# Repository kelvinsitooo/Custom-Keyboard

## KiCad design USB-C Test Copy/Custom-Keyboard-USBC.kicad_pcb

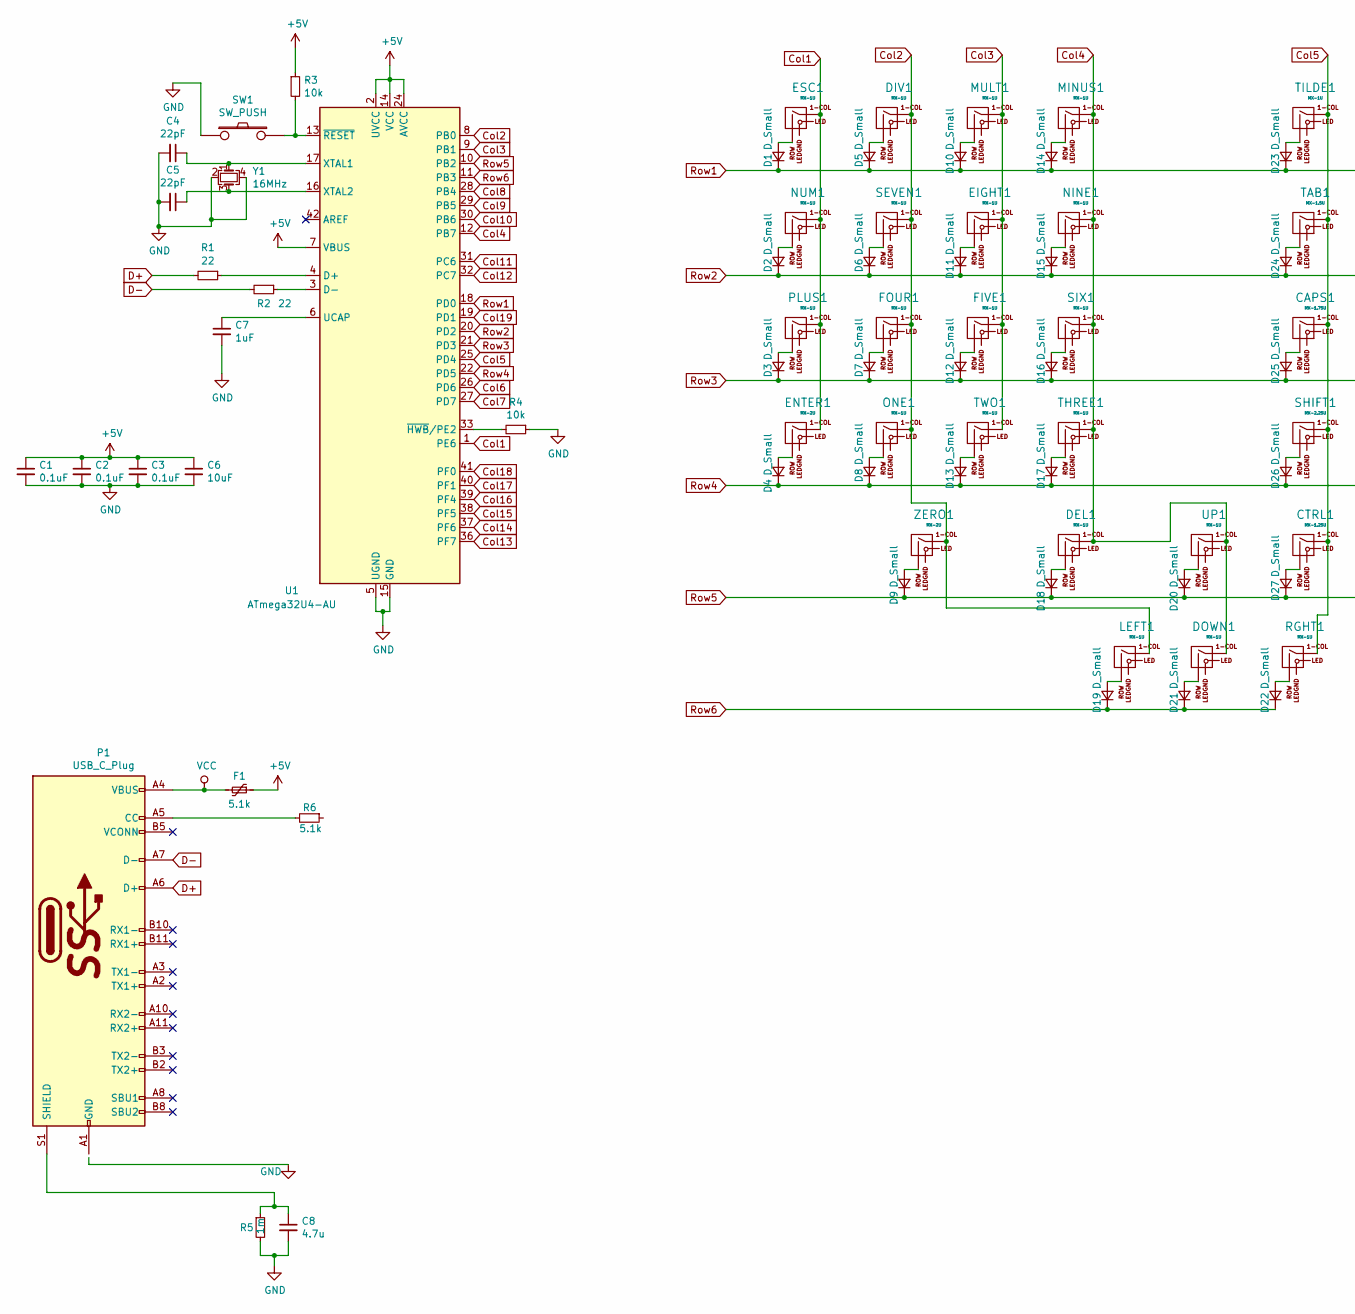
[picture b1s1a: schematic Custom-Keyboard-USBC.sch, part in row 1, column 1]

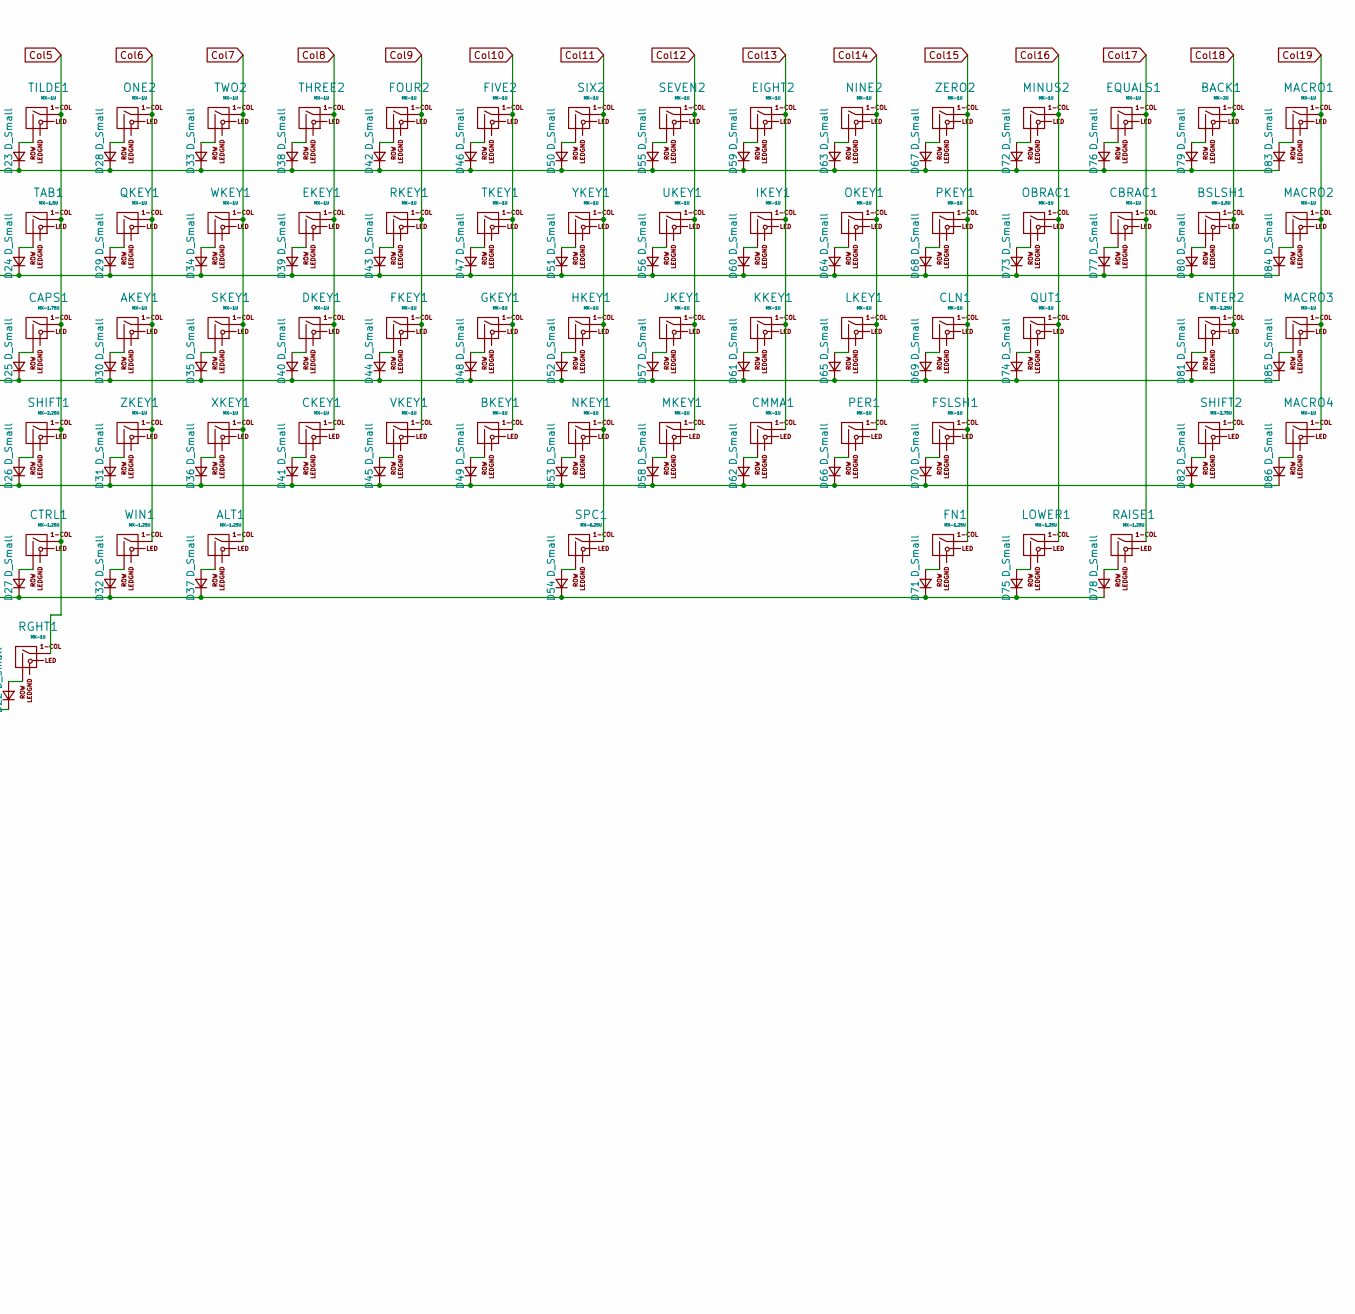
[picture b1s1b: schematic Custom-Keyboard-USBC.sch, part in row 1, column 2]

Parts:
AKEY1: MX-1U; MXOnly-1U-NoLED
ALT1: MX-1.25U; MXOnly-1.25U-NoLED
BACK1: MX-2U; MXOnly-2U-NoLED
BKEY1: MX-1U; MXOnly-1U-NoLED
BSLSH1: MX-1.5U; MXOnly-1.5U-NoLED
C1, C2, C3: 0.1uF; C_0805_2012Metric
C4, C5: 22pF; C_0805_2012Metric
C6: 10uF; C_0805_2012Metric
C7: 1uF; C_0805_2012Metric
C8: 4.7u; C_0805_2012Metric
CAPS1: MX-1.75U; MXOnly-1.75U-NoLED
CBRAC1: MX-1U; MXOnly-1U-NoLED
CKEY1: MX-1U; MXOnly-1U-NoLED
CLN1: MX-1U; MXOnly-1U-NoLED
CMMA1: MX-1U; MXOnly-1U-NoLED
CTRL1: MX-1.25U; MXOnly-1.25U-NoLED
D1, D2, D3, D4, D5, D6, D7, D8, D9, D10, D11, D12, D13, D14, D15, D16, D17, D18, D19, D20, D21, D22, D23, D24, D25, D26, D27, D28, D29, D30, D31, D32, D33, D34, D35, D36, D37, D38, D39, D40, D41, D42, D43, D44, D45, D46, D47, D48, D49, D50, D51, D52, D53, D54, D55, D56, D57, D58, D59, D60, D61, D62, D63, D64, D65, D66, D67, D68, D69, D70, D71, D72, D73, D74, D75, D76, D77, D78, D79, D80, D81, D82, D83, D84, D85, D86: D_Small; D_SOD-123
DEL1: MX-1U; MXOnly-1U-NoLED
DIV1: MX-1U; MXOnly-1U-NoLED
DKEY1: MX-1U; MXOnly-1U-NoLED
DOWN1: MX-1U; MXOnly-1U-NoLED
EIGHT1, EIGHT2: MX-1U; MXOnly-1U-NoLED
EKEY1: MX-1U; MXOnly-1U-NoLED
ENTER1: MX-2U; MXOnly-2U-NoLED
ENTER2: MX-2.25U; MXOnly-2.25U-NoLED
EQUALS1: MX-1U; MXOnly-1U-NoLED
ESC1: MX-1U; MXOnly-1U-NoLED
F1: 5.1k; Fuse_1206_3216Metric
FIVE1, FIVE2: MX-1U; MXOnly-1U-NoLED
FKEY1: MX-1U; MXOnly-1U-NoLED
FN1: MX-1.25U; MXOnly-1.25U-NoLED
FOUR1, FOUR2: MX-1U; MXOnly-1U-NoLED
FSLSH1: MX-1U; MXOnly-1U-NoLED
GKEY1: MX-1U; MXOnly-1U-NoLED
HKEY1: MX-1U; MXOnly-1U-NoLED
IKEY1: MX-1U; MXOnly-1U-NoLED
JKEY1: MX-1U; MXOnly-1U-NoLED
KKEY1: MX-1U; MXOnly-1U-NoLED
LEFT1: MX-1U; MXOnly-1U-NoLED
LKEY1: MX-1U; MXOnly-1U-NoLED
LOWER1: MX-1.25U; MXOnly-1.25U-NoLED
MACRO1, MACRO2, MACRO3, MACRO4: MX-1U; MXOnly-1U-NoLED
MINUS1, MINUS2: MX-1U; MXOnly-1U-NoLED
MKEY1: MX-1U; MXOnly-1U-NoLED
MULT1: MX-1U; MXOnly-1U-NoLED
NINE1, NINE2: MX-1U; MXOnly-1U-NoLED
NKEY1: MX-1U; MXOnly-1U-NoLED
NUM1: MX-1U; MXOnly-1U-NoLED
OBRAC1: MX-1U; MXOnly-1U-NoLED
OKEY1: MX-1U; MXOnly-1U-NoLED
ONE1, ONE2: MX-1U; MXOnly-1U-NoLED
P1: USB_C_Plug; USB-C-12-Pin-MidMount
PER1: MX-1U; MXOnly-1U-NoLED
PKEY1: MX-1U; MXOnly-1U-NoLED
PLUS1: MX-1U; MXOnly-1U-NoLED
QKEY1: MX-1U; MXOnly-1U-NoLED
QUT1: MX-1U; MXOnly-1U-NoLED
R1, R2: 22; R_0805_2012Metric
R3, R4: 10k; R_0805_2012Metric
R5: 1m; R_0805_2012Metric
R6: 5.1k; R_0805_2012Metric
RAISE1: MX-1.25U; MXOnly-1.25U-NoLED
RGHT1: MX-1U; MXOnly-1U-NoLED
RKEY1: MX-1U; MXOnly-1U-NoLED
SEVEN1, SEVEN2: MX-1U; MXOnly-1U-NoLED
SHIFT1: MX-2.25U; MXOnly-2.25U-NoLED
SHIFT2: MX-2.75U; MXOnly-2.75U-NoLED
SIX1, SIX2: MX-1U; MXOnly-1U-NoLED
SKEY1: MX-1U; MXOnly-1U-NoLED
SPC1: MX-6.25U; MXOnly-6.25U-NoLED
SW1: SW_PUSH; SKQG-1155865
TAB1: MX-1.5U; MXOnly-1.5U-NoLED
THREE1, THREE2: MX-1U; MXOnly-1U-NoLED
TILDE1: MX-1U; MXOnly-1U-NoLED
TKEY1: MX-1U; MXOnly-1U-NoLED
TWO1, TWO2: MX-1U; MXOnly-1U-NoLED
U1: ATmega32U4-AU; ATMEGA32U4-AU
UKEY1: MX-1U; MXOnly-1U-NoLED
UP1: MX-1U; MXOnly-1U-NoLED
VKEY1: MX-1U; MXOnly-1U-NoLED
WIN1: MX-1.25U; MXOnly-1.25U-NoLED
WKEY1: MX-1U; MXOnly-1U-NoLED
XKEY1: MX-1U; MXOnly-1U-NoLED
Y1: 16MHz; Crystal_SMD_3225-4Pin_3.2x2.5mm
YKEY1: MX-1U; MXOnly-1U-NoLED
ZERO1: MX-2U; MXOnly-2U-NoLED
ZERO2: MX-1U; MXOnly-1U-NoLED
ZKEY1: MX-1U; MXOnly-1U-NoLED

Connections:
+5V: C1.1, C2.1, C3.1, C6.1, F1.1, R3.1, U1.2 (UVCC), U1.7 (VBUS), U1.14 (VCC), U1.24 (AVCC), U1.34 (VCC), U1.44 (AVCC)
Col1: ENTER1.1 (COL), ESC1.1 (COL), NUM1.1 (COL), PLUS1.1 (COL), U1.1 (PE6)
Col2: DIV1.1 (COL), FOUR1.1 (COL), LEFT1.1 (COL), ONE1.1 (COL), SEVEN1.1 (COL), U1.8 (PB0), ZERO1.1 (COL)
Col3: EIGHT1.1 (COL), FIVE1.1 (COL), MULT1.1 (COL), TWO1.1 (COL), U1.9 (PB1)
Col4: DEL1.1 (COL), DOWN1.1 (COL), MINUS1.1 (COL), NINE1.1 (COL), SIX1.1 (COL), THREE1.1 (COL), U1.12 (PB7), UP1.1 (COL)
Col5: CAPS1.1 (COL), CTRL1.1 (COL), RGHT1.1 (COL), SHIFT1.1 (COL), TAB1.1 (COL), TILDE1.1 (COL), U1.25 (PD4)
Col6: AKEY1.1 (COL), ONE2.1 (COL), QKEY1.1 (COL), U1.26 (PD6), WIN1.1 (COL), ZKEY1.1 (COL)
Col7: ALT1.1 (COL), SKEY1.1 (COL), TWO2.1 (COL), U1.27 (PD7), WKEY1.1 (COL), XKEY1.1 (COL)
Col8: CKEY1.1 (COL), DKEY1.1 (COL), EKEY1.1 (COL), THREE2.1 (COL), U1.28 (PB4)
Col9: FKEY1.1 (COL), FOUR2.1 (COL), RKEY1.1 (COL), U1.29 (PB5), VKEY1.1 (COL)
Col10: BKEY1.1 (COL), FIVE2.1 (COL), GKEY1.1 (COL), TKEY1.1 (COL), U1.30 (PB6)
Col11: HKEY1.1 (COL), NKEY1.1 (COL), SIX2.1 (COL), SPC1.1 (COL), U1.31 (PC6), YKEY1.1 (COL)
Col12: JKEY1.1 (COL), MKEY1.1 (COL), SEVEN2.1 (COL), U1.32 (PC7), UKEY1.1 (COL)
Col13: CMMA1.1 (COL), EIGHT2.1 (COL), IKEY1.1 (COL), KKEY1.1 (COL), U1.36 (PF7)
Col14: LKEY1.1 (COL), NINE2.1 (COL), OKEY1.1 (COL), PER1.1 (COL), U1.37 (PF6)
Col15: CLN1.1 (COL), FN1.1 (COL), FSLSH1.1 (COL), PKEY1.1 (COL), U1.38 (PF5), ZERO2.1 (COL)
Col16: LOWER1.1 (COL), MINUS2.1 (COL), OBRAC1.1 (COL), QUT1.1 (COL), U1.39 (PF4)
Col17: CBRAC1.1 (COL), EQUALS1.1 (COL), RAISE1.1 (COL), U1.40 (PF1)
Col18: BACK1.1 (COL), BSLSH1.1 (COL), ENTER2.1 (COL), SHIFT2.1 (COL), U1.41 (PF0)
Col19: MACRO1.1 (COL), MACRO2.1 (COL), MACRO3.1 (COL), MACRO4.1 (COL), U1.19 (PD1)
D+: P1.A6 (D+), R1.2
D-: P1.A7 (D-), R2.2
GND: C1.2, C2.2, C3.2, C4.2, C5.2, C6.2, C7.2, C8.2, R4.1, R5.2, SW1.1, U1.5 (UGND), U1.15 (GND), U1.23 (GND), U1.35 (GND), U1.43 (GND), Y1.2, Y1.4
unnamed: AKEY1.2 (ROW), D30.2 (A)
unnamed: ALT1.2 (ROW), D37.2 (A)
unnamed: BACK1.2 (ROW), D79.2 (A)
unnamed: BKEY1.2 (ROW), D49.2 (A)
unnamed: BSLSH1.2 (ROW), D80.2 (A)
unnamed: C4.1, U1.17 (XTAL1), Y1.1
unnamed: C5.1, U1.16 (XTAL2), Y1.3
unnamed: C7.1, U1.6 (UCAP)
unnamed: C8.1, P1.S1 (SHIELD), R5.1
unnamed: CAPS1.2 (ROW), D25.2 (A)
unnamed: CBRAC1.2 (ROW), D77.2 (A)
unnamed: CKEY1.2 (ROW), D41.2 (A)
unnamed: CLN1.2 (ROW), D69.2 (A)
unnamed: CMMA1.2 (ROW), D62.2 (A)
unnamed: CTRL1.2 (ROW), D27.2 (A)
unnamed: D1.2 (A), ESC1.2 (ROW)
unnamed: D2.2 (A), NUM1.2 (ROW)
unnamed: D3.2 (A), PLUS1.2 (ROW)
unnamed: D4.2 (A), ENTER1.2 (ROW)
unnamed: D5.2 (A), DIV1.2 (ROW)
unnamed: D6.2 (A), SEVEN1.2 (ROW)
unnamed: D7.2 (A), FOUR1.2 (ROW)
unnamed: D8.2 (A), ONE1.2 (ROW)
unnamed: D9.2 (A), ZERO1.2 (ROW)
unnamed: D10.2 (A), MULT1.2 (ROW)
unnamed: D11.2 (A), EIGHT1.2 (ROW)
unnamed: D12.2 (A), FIVE1.2 (ROW)
unnamed: D13.2 (A), TWO1.2 (ROW)
unnamed: D14.2 (A), MINUS1.2 (ROW)
unnamed: D15.2 (A), NINE1.2 (ROW)
unnamed: D16.2 (A), SIX1.2 (ROW)
unnamed: D17.2 (A), THREE1.2 (ROW)
unnamed: D18.2 (A), DEL1.2 (ROW)
unnamed: D19.2 (A), LEFT1.2 (ROW)
unnamed: D20.2 (A), UP1.2 (ROW)
unnamed: D21.2 (A), DOWN1.2 (ROW)
unnamed: D22.2 (A), RGHT1.2 (ROW)
unnamed: D23.2 (A), TILDE1.2 (ROW)
unnamed: D24.2 (A), TAB1.2 (ROW)
unnamed: D26.2 (A), SHIFT1.2 (ROW)
unnamed: D28.2 (A), ONE2.2 (ROW)
unnamed: D29.2 (A), QKEY1.2 (ROW)
unnamed: D31.2 (A), ZKEY1.2 (ROW)
unnamed: D32.2 (A), WIN1.2 (ROW)
unnamed: D33.2 (A), TWO2.2 (ROW)
unnamed: D34.2 (A), WKEY1.2 (ROW)
unnamed: D35.2 (A), SKEY1.2 (ROW)
unnamed: D36.2 (A), XKEY1.2 (ROW)
unnamed: D38.2 (A), THREE2.2 (ROW)
unnamed: D39.2 (A), EKEY1.2 (ROW)
unnamed: D40.2 (A), DKEY1.2 (ROW)
unnamed: D42.2 (A), FOUR2.2 (ROW)
unnamed: D43.2 (A), RKEY1.2 (ROW)
unnamed: D44.2 (A), FKEY1.2 (ROW)
unnamed: D45.2 (A), VKEY1.2 (ROW)
unnamed: D46.2 (A), FIVE2.2 (ROW)
unnamed: D47.2 (A), TKEY1.2 (ROW)
unnamed: D48.2 (A), GKEY1.2 (ROW)
unnamed: D50.2 (A), SIX2.2 (ROW)
unnamed: D51.2 (A), YKEY1.2 (ROW)
unnamed: D52.2 (A), HKEY1.2 (ROW)
unnamed: D53.2 (A), NKEY1.2 (ROW)
unnamed: D54.2 (A), SPC1.2 (ROW)
unnamed: D55.2 (A), SEVEN2.2 (ROW)
unnamed: D56.2 (A), UKEY1.2 (ROW)
unnamed: D57.2 (A), JKEY1.2 (ROW)
unnamed: D58.2 (A), MKEY1.2 (ROW)
unnamed: D59.2 (A), EIGHT2.2 (ROW)
unnamed: D60.2 (A), IKEY1.2 (ROW)
unnamed: D61.2 (A), KKEY1.2 (ROW)
unnamed: D63.2 (A), NINE2.2 (ROW)
unnamed: D64.2 (A), OKEY1.2 (ROW)
unnamed: D65.2 (A), LKEY1.2 (ROW)
unnamed: D66.2 (A), PER1.2 (ROW)
unnamed: D67.2 (A), ZERO2.2 (ROW)
unnamed: D68.2 (A), PKEY1.2 (ROW)
unnamed: D70.2 (A), FSLSH1.2 (ROW)
unnamed: D71.2 (A), FN1.2 (ROW)
unnamed: D72.2 (A), MINUS2.2 (ROW)
unnamed: D73.2 (A), OBRAC1.2 (ROW)
unnamed: D74.2 (A), QUT1.2 (ROW)
unnamed: D75.2 (A), LOWER1.2 (ROW)
unnamed: D76.2 (A), EQUALS1.2 (ROW)
unnamed: D78.2 (A), RAISE1.2 (ROW)
unnamed: D81.2 (A), ENTER2.2 (ROW)
unnamed: D82.2 (A), SHIFT2.2 (ROW)
unnamed: D83.2 (A), MACRO1.2 (ROW)
unnamed: D84.2 (A), MACRO2.2 (ROW)
unnamed: D85.2 (A), MACRO3.2 (ROW)
unnamed: D86.2 (A), MACRO4.2 (ROW)
unnamed: P1.A1 (GND), P1.A12 (GND), P1.B1 (GND), P1.B12 (GND)
unnamed: P1.A5 (CC), R6.2
unnamed: R1.1, U1.4 (D+)
unnamed: R2.1, U1.3 (D-)
unnamed: R3.2, SW1.2, U1.13 (~RESET)
unnamed: R4.2, U1.33 (~HWB~/PE2)
Row1: D1.1 (K), D5.1 (K), D10.1 (K), D14.1 (K), D23.1 (K), D28.1 (K), D33.1 (K), D38.1 (K), D42.1 (K), D46.1 (K), D50.1 (K), D55.1 (K), D59.1 (K), D63.1 (K), D67.1 (K), D72.1 (K), D76.1 (K), D79.1 (K), D83.1 (K), U1.18 (PD0)
Row2: D2.1 (K), D6.1 (K), D11.1 (K), D15.1 (K), D24.1 (K), D29.1 (K), D34.1 (K), D39.1 (K), D43.1 (K), D47.1 (K), D51.1 (K), D56.1 (K), D60.1 (K), D64.1 (K), D68.1 (K), D73.1 (K), D77.1 (K), D80.1 (K), D84.1 (K), U1.20 (PD2)
Row3: D3.1 (K), D7.1 (K), D12.1 (K), D16.1 (K), D25.1 (K), D30.1 (K), D35.1 (K), D40.1 (K), D44.1 (K), D48.1 (K), D52.1 (K), D57.1 (K), D61.1 (K), D65.1 (K), D69.1 (K), D74.1 (K), D81.1 (K), D85.1 (K), U1.21 (PD3)
Row4: D4.1 (K), D8.1 (K), D13.1 (K), D17.1 (K), D26.1 (K), D31.1 (K), D36.1 (K), D41.1 (K), D45.1 (K), D49.1 (K), D53.1 (K), D58.1 (K), D62.1 (K), D66.1 (K), D70.1 (K), D82.1 (K), D86.1 (K), U1.22 (PD5)
Row5: D9.1 (K), D18.1 (K), D20.1 (K), D27.1 (K), D32.1 (K), D37.1 (K), D54.1 (K), D71.1 (K), D75.1 (K), D78.1 (K), U1.10 (PB2)
Row6: D19.1 (K), D21.1 (K), D22.1 (K), U1.11 (PB3)
VBUS: F1.2, P1.A4 (VBUS), P1.A9 (VBUS), P1.B4 (VBUS), P1.B9 (VBUS)

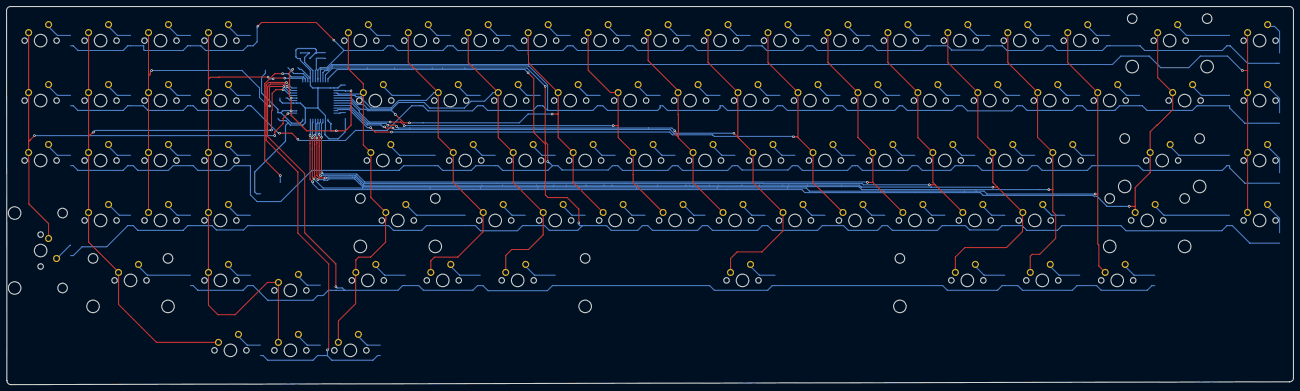
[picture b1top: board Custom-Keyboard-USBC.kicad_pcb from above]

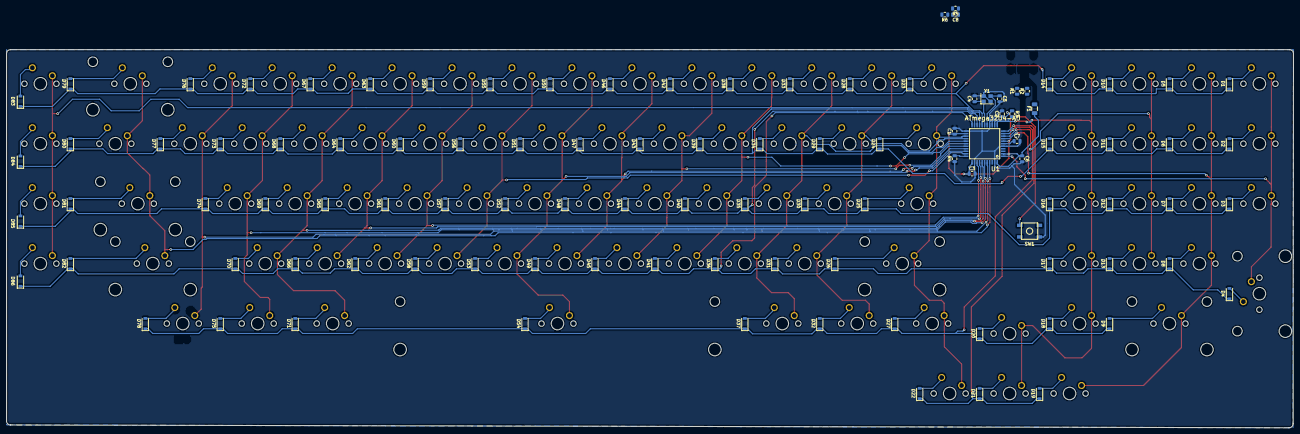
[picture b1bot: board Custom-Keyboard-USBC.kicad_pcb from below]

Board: 2 copper layers, 408.9 x 120.1 mm, 190 parts (104 on the bottom side), 121 nets.

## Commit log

2019-03-22 Initialize Project
    Setting up basic project files.
2019-03-22 Add submodules
2019-03-22 Added Footprint Libraries
2019-03-23 MCU Connections made
    Connected all the MCU connections needed, no Switch/Diode connections.
2019-03-24 Number Pad+Arrow Keys
    Added the number pad plus the arrow keys to the schematic. This actually gives me an idea to do a sort of modular add on to 60%s to convert them to southpaw layouts in a single case.
2019-03-26 Switch Matrix
    Added the full Switch Matrix with Global Labels, with no connections to the Micro-Controller yet.
2019-03-28 Mini-USB Schematic/Footprints
    Added the schematic for the Mini-USB connector, and also mapped them all to Footprints.
2019-03-29 Components Placed onto PCB, no routing
    Placed all the components on to the PCB. have not done the routing yet. Using Mini-USB for now, because I haven't yet learned USB-C.
2019-03-29 Routing
    All components routed and connected to the MCU.
2019-03-29 PCB Size Error Fixing
    Noticed a mistake in the PCB side edge going in to a hole for Stabilizers. Made PCB a little tiny bit bigger to compensate.
2019-03-29 Fill Zones/Gerber FIles
    Fill Zones were added, and Gerber Files were made. All thats left from here is to produce the PCBs if we want to make no changes. I'd like to add USB-C and Underglow RGB LEDs. Might have to change pr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
2019-03-29 Footprint Change - No LEDs
    Schematic has LED pads, but since I don't intend to add LEDs to the keyboard just yet, I changed the footprints to not have any. Don't want there to be any confusion.
2019-03-29 MASSIVE Mess Up fix
    Rebuilt the whole repository from a back up because I screwed up pretty badly when testing USB-C.
2019-04-06 Unsure what changed
